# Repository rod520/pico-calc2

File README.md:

# pico-calc2

A calculator pcb for a Pi-hat like attachment for the Pimoroni Pico LiPo 2 XL W

Could also be used for other pico projects

### Assembly:

solder frames to back of board as necessary (to elevate pico 2 xl above pcb)

solder pico lipo 2 xl onto frame

solder buttons to board (test to make sure all buttons are placed)

insert ribbon connector into ribbon receptacle

insert battery into receptacle

### Images:
#### pcb

#### layers

#### schematic

#### frame
one side of the frame; used to elevate the pico above the board

### BOM:

|component|webpage|notes|
|-|-|-|
|1 x pimoroni pico lipo 2 xl w|[https://shop.pimoroni.com/en-us/products/pimoroni-pico-lipo-2-xl-w?variant=55447911006587 ](https://shop.pimoroni.com/en-us/products/pimoroni-pico-lipo-2-xl-w?variant=55447911006587)||
|60 x (4.5mm x 4.5mm x 3.8mm) buttons|[https://www.amazon.com/100Pcs-Tactile-Actuator-Surface-Momentary/dp/B07CJSV1ZW?psc=1](https://www.amazon.com/100Pcs-Tactile-Actuator-Surface-Momentary/dp/B07CJSV1ZW?psc=1)|any buttons with those dimensions work|
|any lipo battery (tbd)|[https://shop.pimoroni.com/en-us/products/pimoroni-pico-lipo?q=lipo](https://shop.pimoroni.com/en-us/products/pimoroni-pico-lipo?q=lipo)|tbd what battery to use|
|1 x E26RE-RW300-N|[https://www.digikey.com/en/products/detail/focus-lcds/E26RE-RW300-N/20117034](https://www.digikey.com/en/products/detail/focus-lcds/E26RE-RW300-N/20117034)||

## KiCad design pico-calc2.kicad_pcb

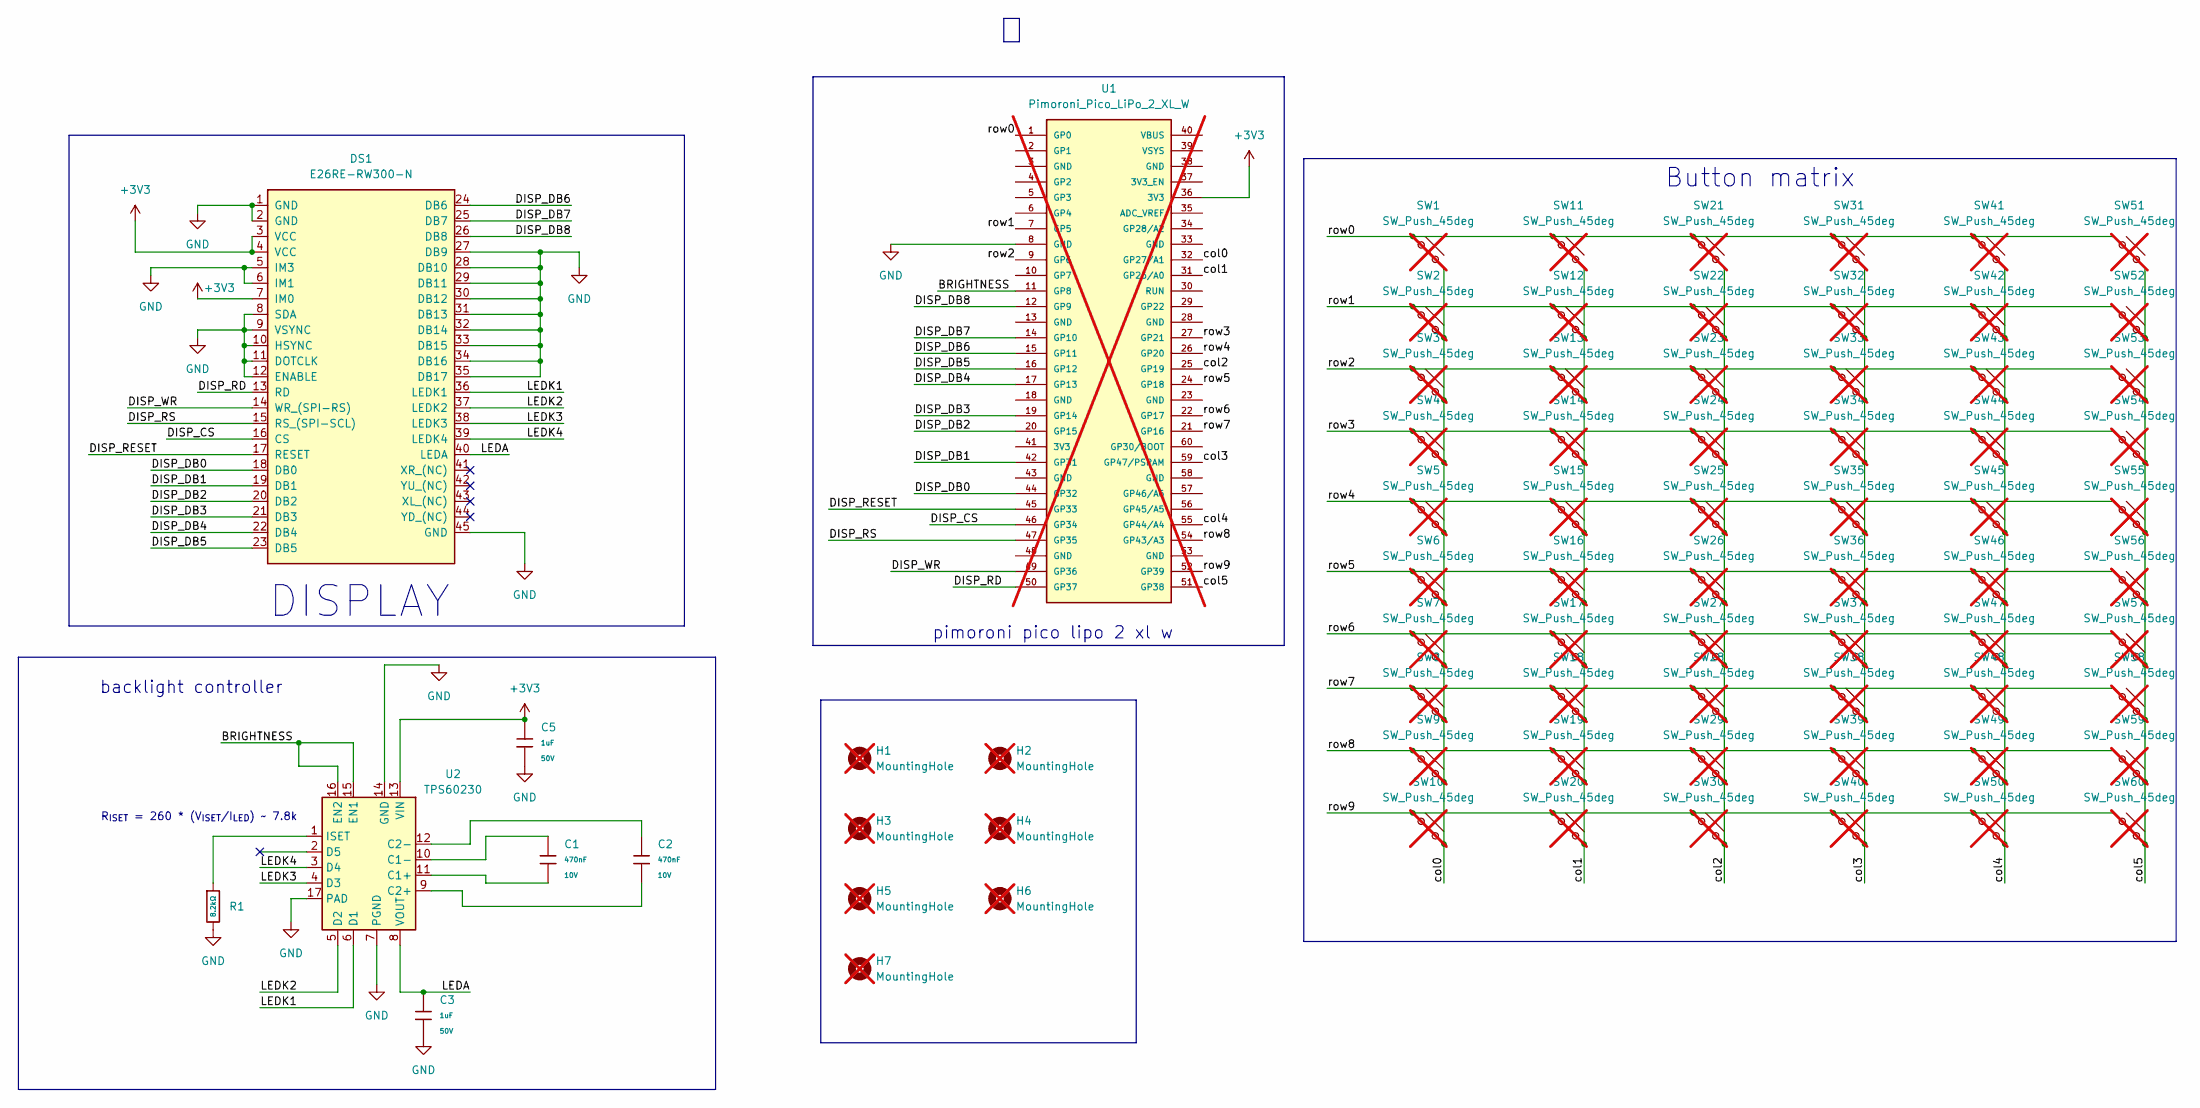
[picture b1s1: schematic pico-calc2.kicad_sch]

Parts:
C1, C2: 470nF; C_0402; Voltage Rated 10V; Tolerance ±10%; Part CL05A474KP5NNNC; LCSC C47339
C3, C5: 1uF; C_0603; Voltage Rated 50V; Tolerance ±10%; Part CL10A105KB8NNNC; LCSC C15849
DS1: E26RE-RW300-N; FPC-SMD_AFC01-S45FCA-00
H1, H2, H3, H4, H5, H6, H7: MountingHole; MountingHole_2.1mm; not fitted
R1: 8.2kΩ; R_0603; Overload Voltage (Max) 75V; Tolerance ±1%; Part 0603WAF8201T5E; LCSC C25981
SW1, SW2, SW3, SW4, SW5, SW6, SW7, SW8, SW9, SW10, SW11, SW12, SW13, SW14, SW15, SW16, SW17, SW18, SW19, SW20, SW21, SW22, SW23, SW24, SW25, SW26, SW27, SW28, SW29, SW30, SW31, SW32, SW33, SW34, SW35, SW36, SW37, SW38, SW39, SW40, SW41, SW42, SW43, SW44, SW45, SW46, SW47, SW48, SW49, SW50, SW51, SW52, SW53, SW54, SW55, SW56, SW57, SW58, SW59, SW60: SW_Push_45deg; SW-SMD_4P-L4.5-W4.5-P3.00-LS7.0; not fitted
U1: Pimoroni_Pico_LiPo_2_XL_W; Pimoroni Pico 2 XL W; not fitted
U2: TPS60230; VQFN-16_L3.0-W3.0-P0.50-TL-EP1.5

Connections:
+3V3: C5.1, DS1.3 (VCC), DS1.4 (VCC), DS1.7 (IM0), U1.36 (3V3), U1.41 (3V3), U2.13 (VIN)
/BRIGHTNESS: U1.11 (GP8), U2.15 (EN1), U2.16 (EN2)
/DISP_CS: DS1.16 (CS), U1.46 (GP34)
/DISP_DB0: DS1.18 (DB0), U1.44 (GP32)
/DISP_DB1: DS1.19 (DB1), U1.42 (GP31)
/DISP_DB2: DS1.20 (DB2), U1.20 (GP15)
/DISP_DB3: DS1.21 (DB3), U1.19 (GP14)
/DISP_DB4: DS1.22 (DB4), U1.17 (GP13)
/DISP_DB5: DS1.23 (DB5), U1.16 (GP12)
/DISP_DB6: DS1.24 (DB6), U1.15 (GP11)
/DISP_DB7: DS1.25 (DB7), U1.14 (GP10)
/DISP_DB8: DS1.26 (DB8), U1.12 (GP9)
/DISP_RD: DS1.13 (RD), U1.50 (GP37)
/DISP_RESET: DS1.17 (RESET), U1.45 (GP33)
/DISP_RS: DS1.15 (RS_(SPI-SCL)), U1.47 (GP35)
/DISP_WR: DS1.14 (WR_(SPI-RS)), U1.49 (GP36)
/LEDA: C3.1, DS1.40 (LEDA), U2.8 (VOUT)
/LEDK1: DS1.36 (LEDK1), U2.6 (D1)
/LEDK2: DS1.37 (LEDK2), U2.5 (D2)
/LEDK3: DS1.38 (LEDK3), U2.4 (D3)
/LEDK4: DS1.39 (LEDK4), U2.3 (D4)
/col0: SW1.2, SW2.2, SW3.2, SW4.2, SW5.2, SW6.2, SW7.2, SW8.2, SW9.2, SW10.2, U1.32 (GP27/A1)
/col1: SW11.2, SW12.2, SW13.2, SW14.2, SW15.2, SW16.2, SW17.2, SW18.2, SW19.2, SW20.2, U1.31 (GP26/A0)
/col2: SW21.2, SW22.2, SW23.2, SW24.2, SW25.2, SW26.2, SW27.2, SW28.2, SW29.2, SW30.2, U1.25 (GP19)
/col3: SW31.2, SW32.2, SW33.2, SW34.2, SW35.2, SW36.2, SW37.2, SW38.2, SW39.2, SW40.2, U1.59 (GP47/PSRAM)
/col4: SW41.2, SW42.2, SW43.2, SW44.2, SW45.2, SW46.2, SW47.2, SW48.2, SW49.2, SW50.2, U1.55 (GP44/A4)
/col5: SW51.2, SW52.2, SW53.2, SW54.2, SW55.2, SW56.2, SW57.2, SW58.2, SW59.2, SW60.2, U1.51 (GP38)
/row0: SW1.1, SW11.1, SW21.1, SW31.1, SW41.1, SW51.1, U1.1 (GP0)
/row1: SW2.1, SW12.1, SW22.1, SW32.1, SW42.1, SW52.1, U1.7 (GP5)
/row2: SW3.1, SW13.1, SW23.1, SW33.1, SW43.1, SW53.1, U1.9 (GP6)
/row3: SW4.1, SW14.1, SW24.1, SW34.1, SW44.1, SW54.1, U1.27 (GP21)
/row4: SW5.1, SW15.1, SW25.1, SW35.1, SW45.1, SW55.1, U1.26 (GP20)
/row5: SW6.1, SW16.1, SW26.1, SW36.1, SW46.1, SW56.1, U1.24 (GP18)
/row6: SW7.1, SW17.1, SW27.1, SW37.1, SW47.1, SW57.1, U1.22 (GP17)
/row7: SW8.1, SW18.1, SW28.1, SW38.1, SW48.1, SW58.1, U1.21 (GP16)
/row8: SW9.1, SW19.1, SW29.1, SW39.1, SW49.1, SW59.1, U1.54 (GP43/A3)
/row9: SW10.1, SW20.1, SW30.1, SW40.1, SW50.1, SW60.1, U1.52 (GP39)
GND: C3.2, C5.2, DS1.1 (GND), DS1.2 (GND), DS1.5 (IM3), DS1.6 (IM1), DS1.8 (SDA), DS1.9 (VSYNC), DS1.10 (HSYNC), DS1.11 (DOTCLK), DS1.12 (ENABLE), DS1.27 (DB9), DS1.28 (DB10), DS1.29 (DB11), DS1.30 (DB12), DS1.31 (DB13), DS1.32 (DB14), DS1.33 (DB15), DS1.34 (DB16), DS1.35 (DB17), DS1.45 (GND), R1.2, U1.3 (GND), U1.8 (GND), U1.13 (GND), U1.18 (GND), U1.23 (GND), U1.28 (GND), U1.33 (GND), U1.38 (GND), U1.43 (GND), U1.48 (GND), U1.53 (GND), U1.58 (GND), U2.7 (PGND), U2.14 (GND), U2.17 (PAD)
unnamed: C1.2, U2.11 (C1+)
unnamed: C1.1, U2.10 (C1-)
unnamed: C2.2, U2.9 (C2+)
unnamed: C2.1, U2.12 (C2-)
unnamed: R1.1, U2.1 (ISET)

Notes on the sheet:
DISPLAY
R_{ISET} = 260 * (V_{ISET}/I_{LED}) ~ 7.8k
Button matrix
backlight controller
pimoroni pico lipo 2 xl w

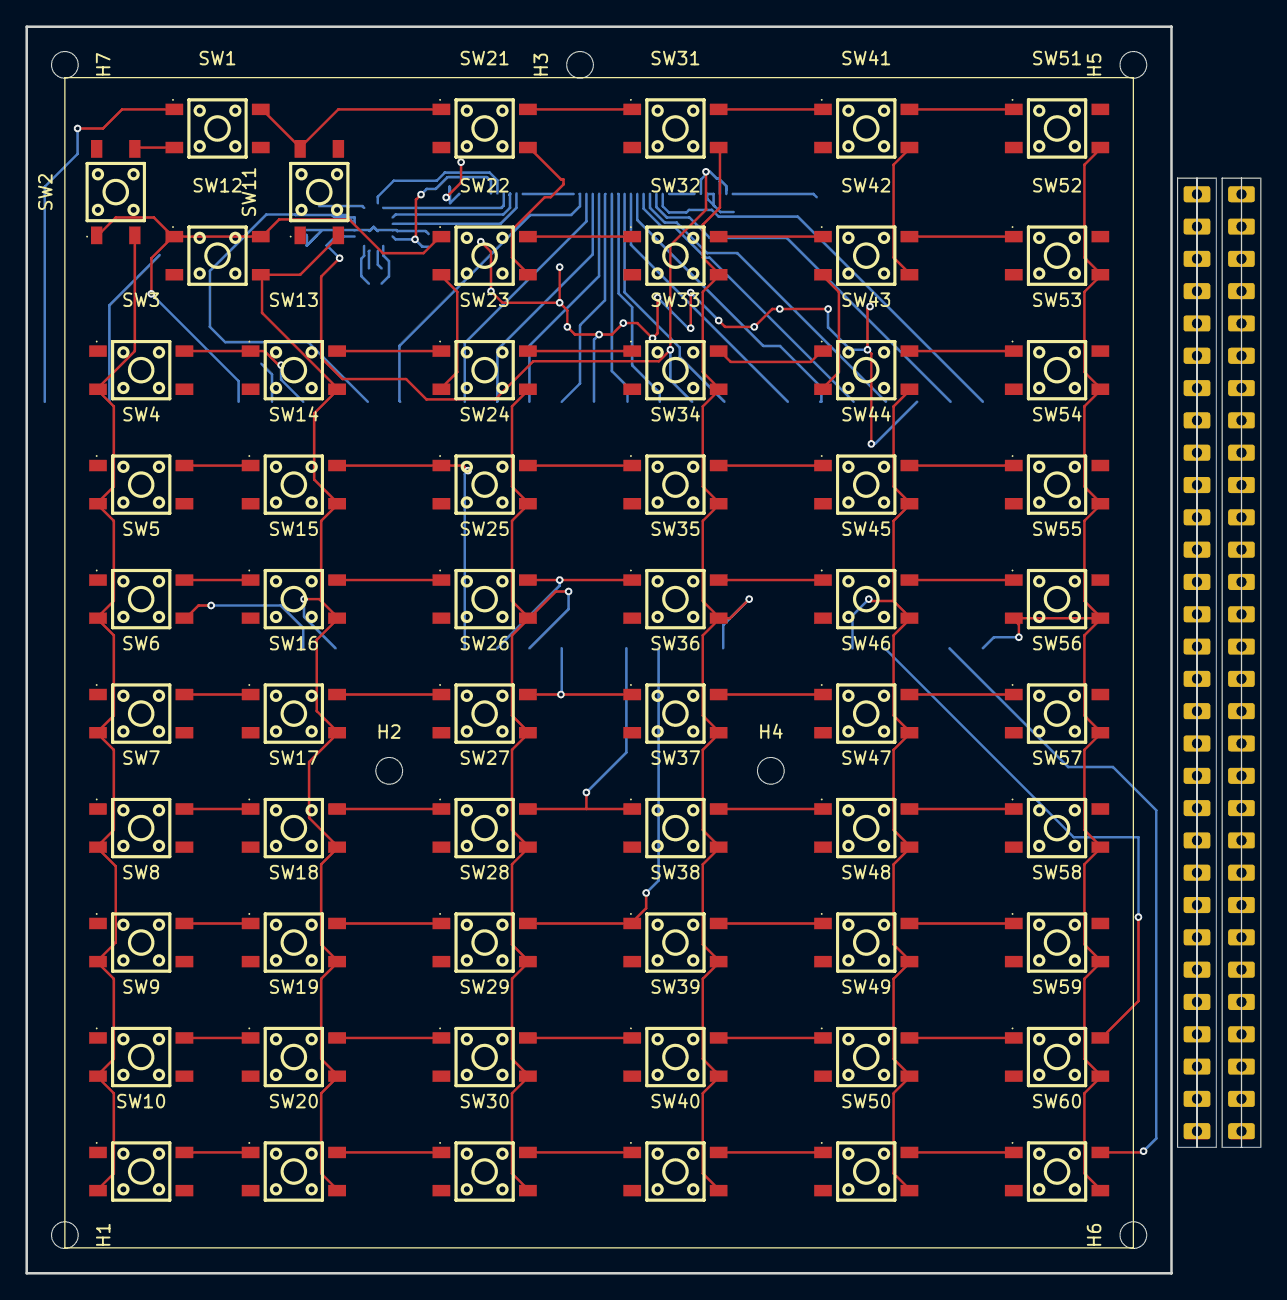
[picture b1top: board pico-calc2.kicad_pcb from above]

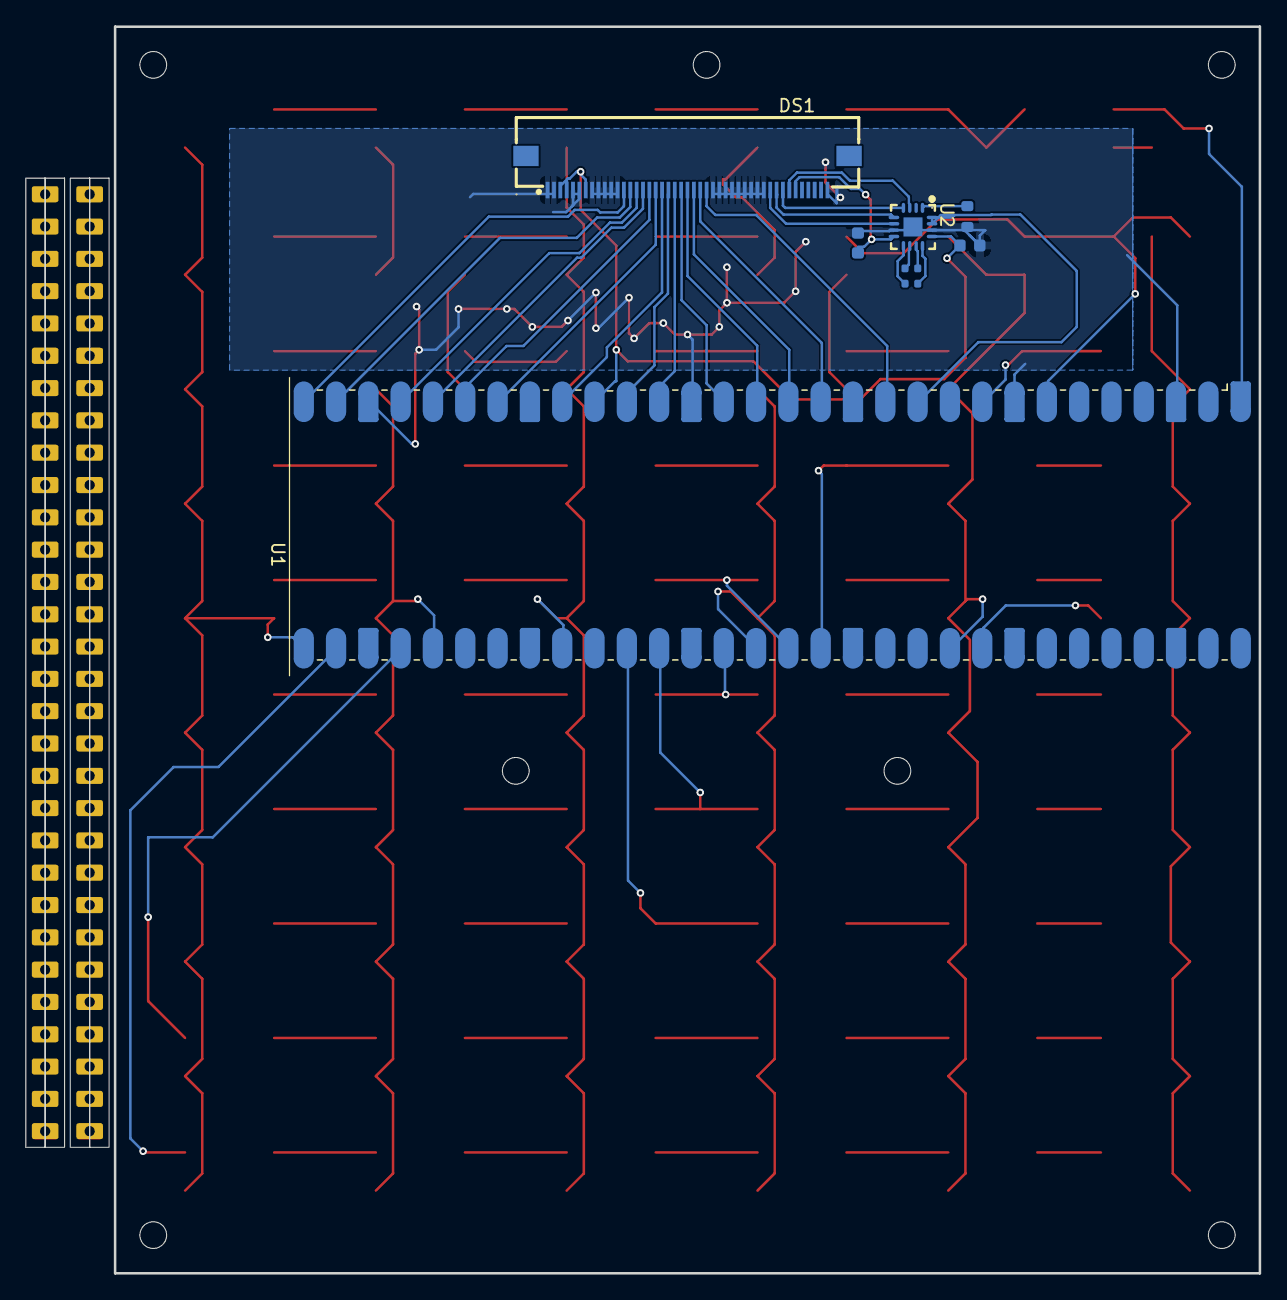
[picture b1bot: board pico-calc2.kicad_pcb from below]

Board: 2 copper layers, 97.0 x 98.0 mm, 75 parts (8 on the bottom side), 43 nets.
